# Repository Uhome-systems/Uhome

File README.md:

- 👋 Hi, I’m @Uhome-Systems
- 🌐 Our website is https://uhome.systems/
- 👀 I’m interested in smart home systems
- 📫 How to reach me info@uhome.systems
- 💬 Join our Discord here: https://discord.gg/JBZaJAvD

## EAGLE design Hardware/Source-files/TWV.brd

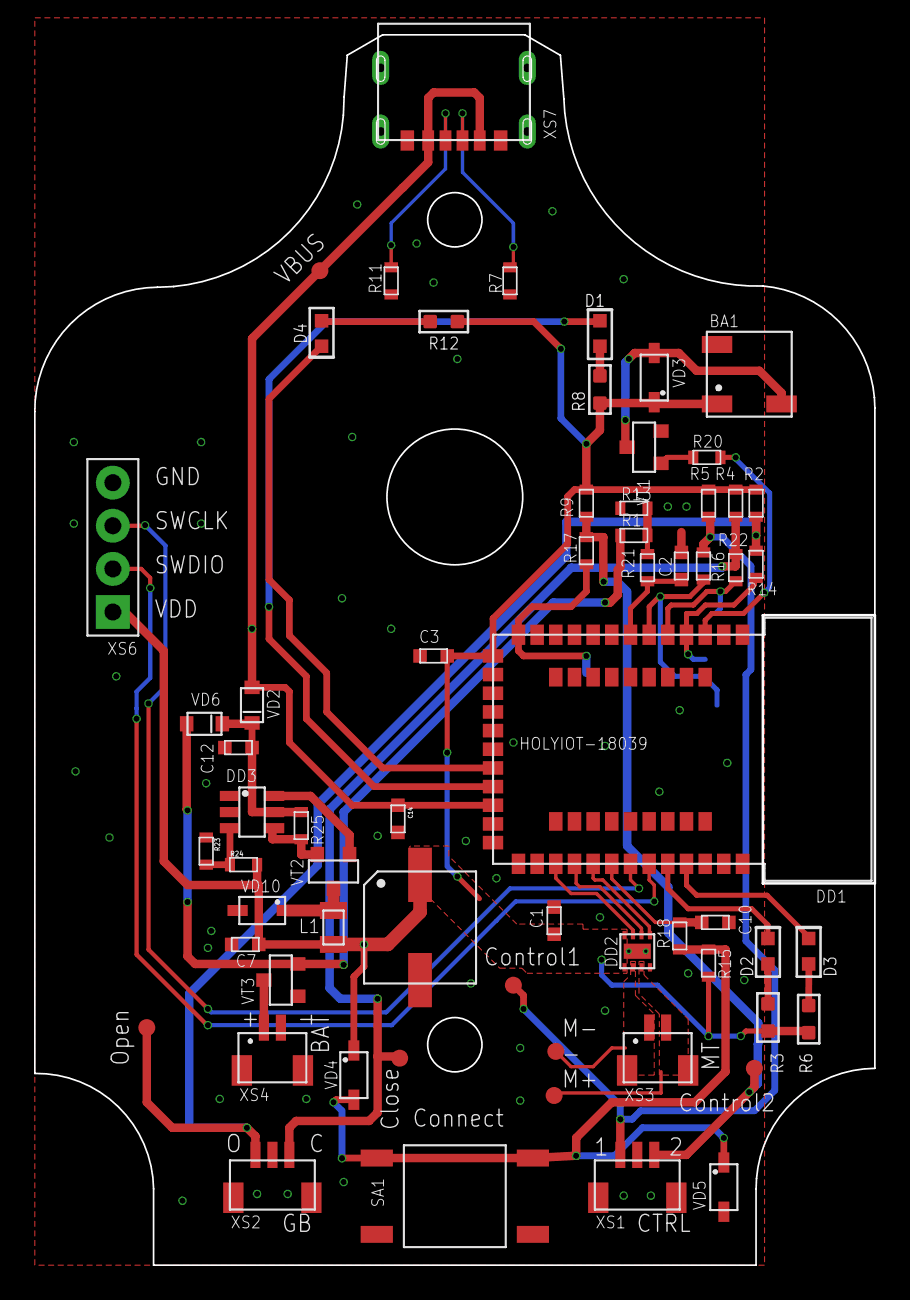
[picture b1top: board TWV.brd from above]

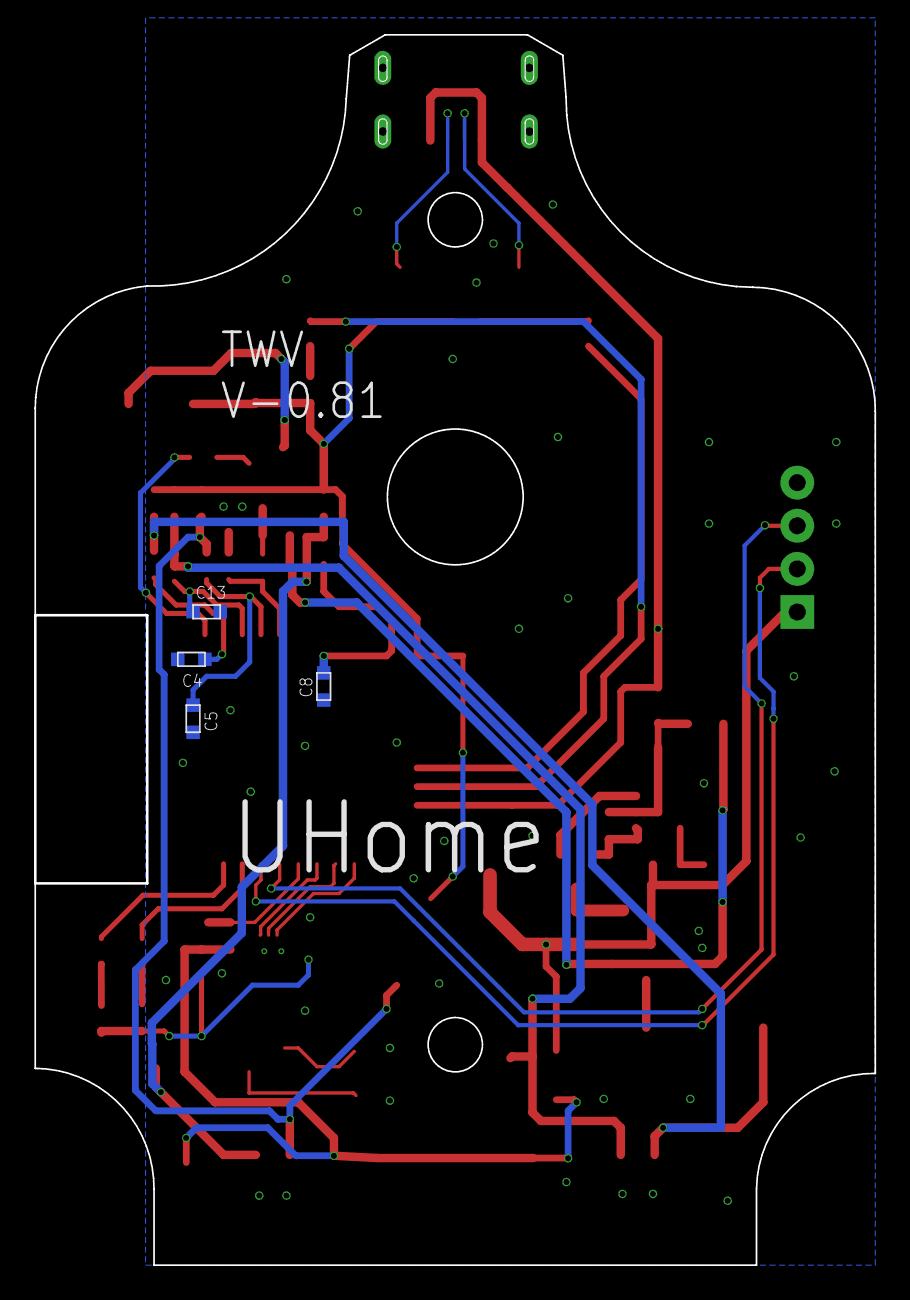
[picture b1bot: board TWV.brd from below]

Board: 2 copper layers, 49.5 x 72.5 mm, 67 parts (4 on the bottom side), 42 nets.

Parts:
BA1: SMD-5025-0340-12Ω
C1, C3, C14: 0.1 uF; 0603
C2: 1 uF; 0603
C4, C5, C8, C10, C13: 1uF; 0603
C6: 220 uF; 6.3X8
C7: 0.47 uF; 0603
C12: 10uF; 0603
D1: BL-HKC37A-AV-TRB; 0603
D2, D3: 150060RS75000; 0603
D4: BL-HB337A-AV-TRB; 0603
DD1: HOLYIOT-18039
DD2: DRV8837CDSGR; WSON-8
DD3: TPS64201DBVR; SOT23-6
L1: MCQ1V2012-4R7-R; 0805
R1, R2, R4, R5, R9, R13, R15: 470 kOhm; 0603
R3, R6, R8, R12: 330; RES0603
R7, R11: 5.1 kOhm; 0603
R14, R16, R17, R18, R22: 1kOhm; 0603
R20: 82; 0603
R21: 1 kOhm; 0603
R23: 360 kOhm; 0603
R24: 620 kOhm; 0603
R25: 33 mOhm; 0603
SA1: K2-1102SP-Z4SC-04
T3, T4, T5, T6, T9, T10, T11: TEST_POINT_2MM
VD2, VD6: SD0805S040S0R5; 0805
VD3, VD4, VD5, VD10: SD103CW-AQ; SOD-123F
VT1: 2SC1623; SOT-23
VT2: SI2333; SOT-23
VT3: IRLML6401; SOT-23
XS1, XS2: BM03B-SRSS-TB
XS3, XS4: BM02B-SRSS-TB
XS6: TH1X4-2.54MM
XS7: 918-418K2023S40026

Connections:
+3.3V: BA1.+, C1.1, C3.1, C6.+, C7.1, DD1.14, DD2.1, DD2.8, L1.P$2, R2.2, R3.1, R4.2, R5.2, R6.1, R8.1, R9.2, R12.1, R15.2, R24.2, VD3.C, VD4.C, XS6.1
BATTERY: C2.1, DD1.7, R21.2
BUTTON: C10.1, DD1.30, R18.2
BUZ: DD1.3, R20.1
CLOSE: C13.1, DD1.5, R22.2
CONTROL: C5.1, DD1.6, R16.2
CONTROL2: C8.1, DD1.13, R17.2
D1: D1.C, DD1.21
D4: D4.C, DD1.20
GND: C1.2, C2.2, C3.2, C4.2, C5.2, C6.-, C7.2, C8.2, C10.2, C12.2, C13.2, C14.2, DD1.1, DD1.25, DD1.37, DD2.4, DD2.GND, DD3.1, DD3.2, R7.1, R11.1, R13.1, R23.1, SA1.1, SA1.4, VD5.A, VD10.A, VT1.2, VT3.1, XS1.2, XS2.2, XS4.2, XS6.4, XS7.A12, XS7.B12, XS7.SH1, XS7.SH2, XS7.SH3, XS7.SH4
IN1: DD1.28, DD2.6
IN2: DD1.29, DD2.5
LED1: D2.C, DD1.33
LED2: D3.C, DD1.34
M+: DD2.3, T9.1, XS3.2
M-: DD2.2, T10.1, XS3.1
unnamed: R15.1, R18.1, SA1.2, SA1.3, VD4.A, VD5.C
unnamed: VT3.3, XS4.1
unnamed: R11.2, XS7.B5
unnamed: BA1.-, VD3.A, VT1.3
unnamed: D1.A, R8.2
unnamed: R7.2, XS7.A5
unnamed: D2.A, R3.2
unnamed: D3.A, R6.2
unnamed: R20.2, VT1.1
unnamed: D4.A, R12.2
unnamed: R1.1, R13.2, R21.1
unnamed: L1.P$1, VD10.C, VT2.3
unnamed: DD3.6, VT2.1
unnamed: DD3.4, R25.2, VT2.2
unnamed: DD3.3, R23.2, R24.1
NSLEEP: DD1.27, DD2.7
OPEN: C4.1, DD1.4, R14.2
SWDCLK: DD1.31, XS6.3
SWDIO: DD1.32, XS6.2
VBAT: R1.2, VD6.1, VT3.2
VBUS: C14.1, DD1.22, T11.1, VD2.1, XS7.A9, XS7.B9
VOUT: C12.1, DD3.5, R25.1, VD2.2, VD6.2
XS1.1: R2.1, R14.1, T4.1, XS2.1
XS1.3: R4.1, R22.1, T5.1, XS2.3
XS2.1: R5.1, R16.1, T3.1, XS1.1
XS2.3: R9.1, R17.1, T6.1, XS1.3

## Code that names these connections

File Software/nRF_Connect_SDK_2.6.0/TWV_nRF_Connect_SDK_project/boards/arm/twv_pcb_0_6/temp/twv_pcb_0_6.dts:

// Copyright (c) 2023 Nordic Semiconductor ASA
// SPDX-License-Identifier: Apache-2.0

/dts-v1/;
#include <nordic/nrf52840_qiaa.dtsi>
#include "twv_pcb_0_6-pinctrl.dtsi"

/ {
	model = "TWV_PCB_0_6";
	compatible = "uhome,twv-pcb-0-6";

	chosen {
		zephyr,console = &uart0;
		zephyr,shell-uart = &uart0;
		zephyr,uart-mcumgr = &uart0;
		zephyr,bt-mon-uart = &uart0;
		zephyr,bt-c2h-uart = &uart0;
		zephyr,sram = &sram0;
		zephyr,flash = &flash0;
		zephyr,code-partition = &slot0_partition;
		zephyr,ieee802154 = &ieee802154;
	};

	buttons {
		compatible = "gpio-keys";
		pairing {
			gpios = <&gpio1 2 (GPIO_ACTIVE_LOW)>;
			label = "Pairing button";
		};

		open {
			gpios = <&gpio1 13 (GPIO_ACTIVE_LOW)>;
			label = "GB Open limmit switch";
		};

		close {
			gpios = <&gpio1 15 (GPIO_ACTIVE_LOW)>;
			label = "GB Close limmit switch";
		};

		contro_1 {
			gpios = <&gpio0 3 (GPIO_ACTIVE_LOW)>;
			label = "Control limmit switch 1";
		};

		control_2 {
			gpios = <&gpio0 5 (GPIO_ACTIVE_LOW)>;
			label = "Control limmit switch 2";
		};
	};

	led_indication {
		compatible = "gpio-leds";
		pairing_led {
			gpios = <&gpio1 4 (GPIO_ACTIVE_LOW)>;
		};

		error_led {
			gpios = <&gpio1 6 (GPIO_ACTIVE_LOW)>;
		};

		open_status_led {
			gpios = <&gpio0 18 (GPIO_ACTIVE_LOW)>;
		};

		close_status_led {
			gpios = <&gpio0 19 0>;
		};
	};
};

&flash0 {

	partitions {
		compatible = "fixed-partitions";
		#address-cells = <1>;
		#size-cells = <1>;

		boot_partition: partition@0 {
			label = "mcuboot";
			reg = <0x00000000 0x0000C000>;
		};
		slot0_partition: partition@c000 {
			label = "image-0";
			reg = <0x0000C000 0x00076000>;
		};
		slot1_partition: partition@82000 {
			label = "image-1";
			reg = <0x00082000 0x00076000>;
		};

		/*
		 * The flash starting at 0x000f8000 and ending at
		 * 0x000fffff is reserved for use by the application.
		 */

		/*
		 * Storage partition will be used by FCB/LittleFS/NVS
		 * if enabled.
		 */
		storage_partition: partition@f8000 {
			label = "storage";
			reg = <0x000f8000 0x00008000>;
		};
	};
};

&adc {
    status = "okay";
};

&gpio0 {
    status = "okay";
};

&gpio1 {
    status = "okay";
};

&gpiote {
    status = "okay";
};

&uart1 {
	current-speed = <115200>;
	pinctrl-0 = <&uart1_default>;
	pinctrl-1 = <&uart1_sleep>;
	pinctrl-names = "default", "sleep";
};

&uart0 {
	compatible = "nordic,nrf-uarte";
	status = "okay";
	current-speed = <115200>;
	pinctrl-0 = <&uart0_default>;
	pinctrl-1 = <&uart0_sleep>;
	pinctrl-names = "default", "sleep";
};

&systick {
    status = "okay";
};

&timer4 {
    status = "okay";
};

&timer3 {
    status = "okay";
};

&timer2 {
    status = "okay";
};

&timer1 {
    status = "okay";
};

&timer0 {
    status = "okay";
};

&rtc0 {
    status = "okay";
};

&rtc1 {
    status = "okay";
};

&rtc2 {
    status = "okay";
};

&i2c0 {
	compatible = "nordic,nrf-twi";
	status = "okay";
	pinctrl-0 = <&i2c0_default>;
	pinctrl-1 = <&i2c0_sleep>;
	pinctrl-names = "default", "sleep";
};

&i2c1 {
	compatible = "nordic,nrf-twi";
	/* Cannot be used together with spi1. */
	/* status = "okay"; */
	pinctrl-0 = <&i2c1_default>;
	pinctrl-1 = <&i2c1_sleep>;
	pinctrl-names = "default", "sleep";
};

&pwm0 {
	status = "okay";
	pinctrl-0 = <&pwm0_default>;
	pinctrl-1 = <&pwm0_sleep>;
	pinctrl-names = "default", "sleep";
};

&spi0 {
	compatible = "nordic,nrf-spi";
	/* Cannot be used together with i2c0. */
	/* status = "okay"; */
	pinctrl-0 = <&spi0_default>;
	pinctrl-1 = <&spi0_sleep>;
	pinctrl-names = "default", "sleep";
};

&spi1 {
	compatible = "nordic,nrf-spi";
	status = "okay";
	pinctrl-0 = <&spi1_default>;
	pinctrl-1 = <&spi1_sleep>;
	pinctrl-names = "default", "sleep";
};

&spi2 {
	compatible = "nordic,nrf-spi";
	status = "disabled";
	pinctrl-0 = <&spi2_default>;
	pinctrl-1 = <&spi2_sleep>;
	pinctrl-names = "default", "sleep";
};

&qspi {
	status = "okay";
	pinctrl-0 = <&qspi_default>;
	pinctrl-1 = <&qspi_sleep>;
	pinctrl-names = "default", "sleep";
	mx25r64: mx25r6435f@0 {
		compatible = "nordic,qspi-nor";
		reg = <0>;
		/* MX25R64 supports only pp and pp4io */
		writeoc = "pp4io";
		/* MX25R64 supports all readoc options */
		readoc = "read4io";
		sck-frequency = <8000000>;
		jedec-id = [c2 28 17];
		sfdp-bfp = [
			e5 20 f1 ff  ff ff ff 03  44 eb 08 6b  08 3b 04 bb
			ee ff ff ff  ff ff 00 ff  ff ff 00 ff  0c 20 0f 52
			10 d8 00 ff  23 72 f5 00  82 ed 04 cc  44 83 68 44
			30 b0 30 b0  f7 c4 d5 5c  00 be 29 ff  f0 d0 ff ff
		];
		size = <67108864>;
		has-dpd;
		t-enter-dpd = <10000>;
		t-exit-dpd = <35000>;
	};
};

&ieee802154 {
	status = "okay";
};

zephyr_udc0: &usbd {
	compatible = "nordic,nrf-usbd";
	status = "okay";
};

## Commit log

2023-11-08 Add files via upload
    Initial commit
2023-11-08 Software initial commit
2023-11-09 Schematic update
2023-11-10 Hardware source files
2023-11-13 Add parts in stl format
2024-01-16 Testing bug fixes
2024-01-18 Version number fix
2024-01-18 remove old FOTA pack
2024-01-24 Stable PCB version
2024-04-14 update PCB to V0.96
    PCB development moved from Eagle to KiCAD.
2024-04-14 Firmware version update to V2.24
    Firmware development moved to nRF Connect SDK 2.6.0
